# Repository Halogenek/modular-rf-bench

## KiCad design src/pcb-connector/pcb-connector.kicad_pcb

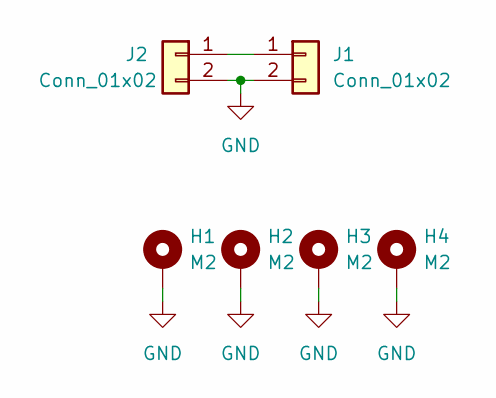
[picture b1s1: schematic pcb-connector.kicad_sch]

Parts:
H1, H2, H3, H4: M2; M2-hole
J1, J2: Conn_01x02; edge-connector

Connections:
GND: H1.1, H2.1, H3.1, H4.1, J1.2, J2.2
unnamed: J1.1, J2.1

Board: 2 copper layers, 6 parts (0 on the bottom side), 2 nets, no tracks yet.

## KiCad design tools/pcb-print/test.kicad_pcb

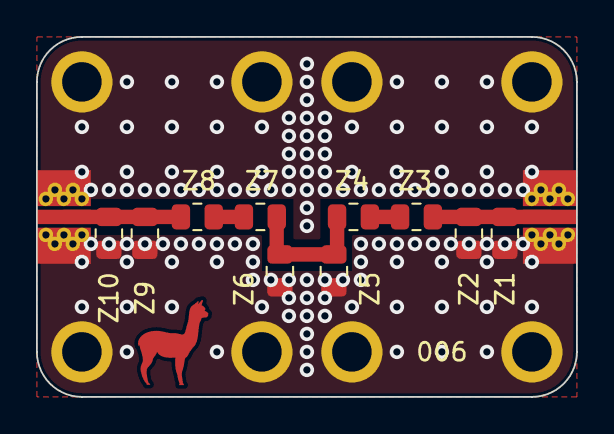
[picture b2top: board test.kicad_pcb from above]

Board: 2 copper layers, 30.0 x 20.0 mm, 20 parts (0 on the bottom side), 6 nets.

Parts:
H1, H2, H3, H4, H5, H6, H7, H8: M2; M2-hole
J1, J2: CONN; edge-connector
Z1, Z2, Z3, Z4, Z5, Z6, Z7, Z8, Z9, Z10: Z; R_0805_2012Metric

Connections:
GND: H1.1, H2.1, H3.1, H4.1, H5.1, H6.1, H7.1, H8.1, J1.2, J2.2, Z1.2, Z2.2, Z5.2, Z6.2, Z9.2, Z10.2
unnamed: J1.1, Z1.1, Z2.1, Z3.1
unnamed: J2.1, Z8.2, Z9.1, Z10.1
unnamed: Z3.2, Z4.1
unnamed: Z4.2, Z5.1, Z6.1, Z7.1
unnamed: Z7.2, Z8.1
